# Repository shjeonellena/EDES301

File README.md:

# EDES301
EDES 301 Repository

# HexaForm Actuator Keyboard Test

This project provides a simple **keyboard-driven test interface** for the HexaForm prototype.  
Using a BeagleBone and GPIO control, you can:

- Turn an **air pump** on and off  
- Toggle **two solenoid valves** (Formation 1 and Formation 2)  
- See the current state and hints on a **16x2 HD44780 LCD** with an I²C backpack

It’s meant as a quick way to verify that wiring, drivers, and actuators are working as expected.

---

## Features

- Keyboard commands to control:
  - Pump (ON/OFF)
  - Solenoid 1 (Formation 1)
  - Solenoid 2 (Formation 2)
- Live status feedback on the HD44780 display:
  - Shows current action (e.g., `Pump ON`, `Formation 1`, `Turning off...`)
  - Shows which key to press to switch states (e.g., `OFF --> 2`)
- Safe shutdown:
  - Turns off all actuators
  - Clears the LCD and turns off the backlight
  - Calls `GPIO.cleanup()` on exit

---

## Hardware Overview

**Controller:**
- BeagleBone (e.g., BeagleBone Black / PocketBeagle)  
- GPIO pins used:
  - `P2_2` → Air pump (via ULN driver input)
  - `P2_4` → Solenoid 1 (via ULN driver input)
  - `P2_6` → Solenoid 2 (via ULN driver input)

**Actuation:**
- 1× Air pump
- 2× Solenoid valves  
- 1× ULN transistor array / driver (e.g., ULN2803A or similar) between GPIO and actuators
- External power supply for pump and solenoids (do **not** power them directly from the BeagleBone pins)

**Display:**
- HD44780-compatible 16x2 character LCD
- I²C backpack (e.g., PCF8574T)
- Connected to I²C bus on the BeagleBone
- Controlled via the `hd44780` CircuitPython-style library

---

## Software Requirements

On the BeagleBone:

- Python 3
- [`Adafruit_BBIO`](https://github.com/adafruit/adafruit-beaglebone-io-python) for GPIO
- `hd44780` (https://github.com/bablokb/circuitpython-hd44780/tree/master) library for controlling the LCD (the one used in:
  ```python
  import hd44780
  display = hd44780.HD44780()
  ```)

Make sure these are installed and importable in Python before running the script.

---

## File

The main script (for example):

```bash
actuator_keyboard_test.py

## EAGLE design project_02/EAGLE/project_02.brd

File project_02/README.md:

# Etch-A-Sketch PCB Design

This directory contains all design and manufacturing files for **Project 02**, which focuses on creating a custom printed circuit board (PCB) for the Etch-A-Sketch project. The board was designed to interface with a **PocketBeagle** and supports the electronics required for the implemented system.

All files necessary for **PCB fabrication, assembly, and documentation** are included in this repository.

---

## Repository Structure

### `/docs`
This folder contains supporting documentation for Project 02, including:
- The **Project 02 proposal**, outlining the design concept and system goals
- A **mechanical block diagram** describing the overall system architecture
- A **PDF of the finalized schematics**
- Images of the **layers** of the PCB layout for reference and review

---

### `/EAGLE`
This folder contains the full EAGLE design files used to create the PCB:
- **`.lbr`** – Custom and modified component libraries
- **`.sch`** – Schematic files defining the electrical design
- **`.brd`** – Board layout files defining component placement and routing

#### `/EAGLE/CAM Output`
The subfolder contains manufacturing outputs generated using **EAGLE’s default CAM settings**, including:
- **Gerber files** for PCB fabrication
- **Drill files** for vias and through-holes
- **Assembly files** for component placement and reference

These files can be directly submitted to a PCB manufacturer for production.

---

## Notes
- The PCB was designed with standard fabrication constraints in mind
- All silkscreen, copper, and drill layers have been verified prior to Gerber generation
- No additional processing is required before manufacturing

---

## Author
Ellena Jeon
Etch-A-Sketch Project – Project 02

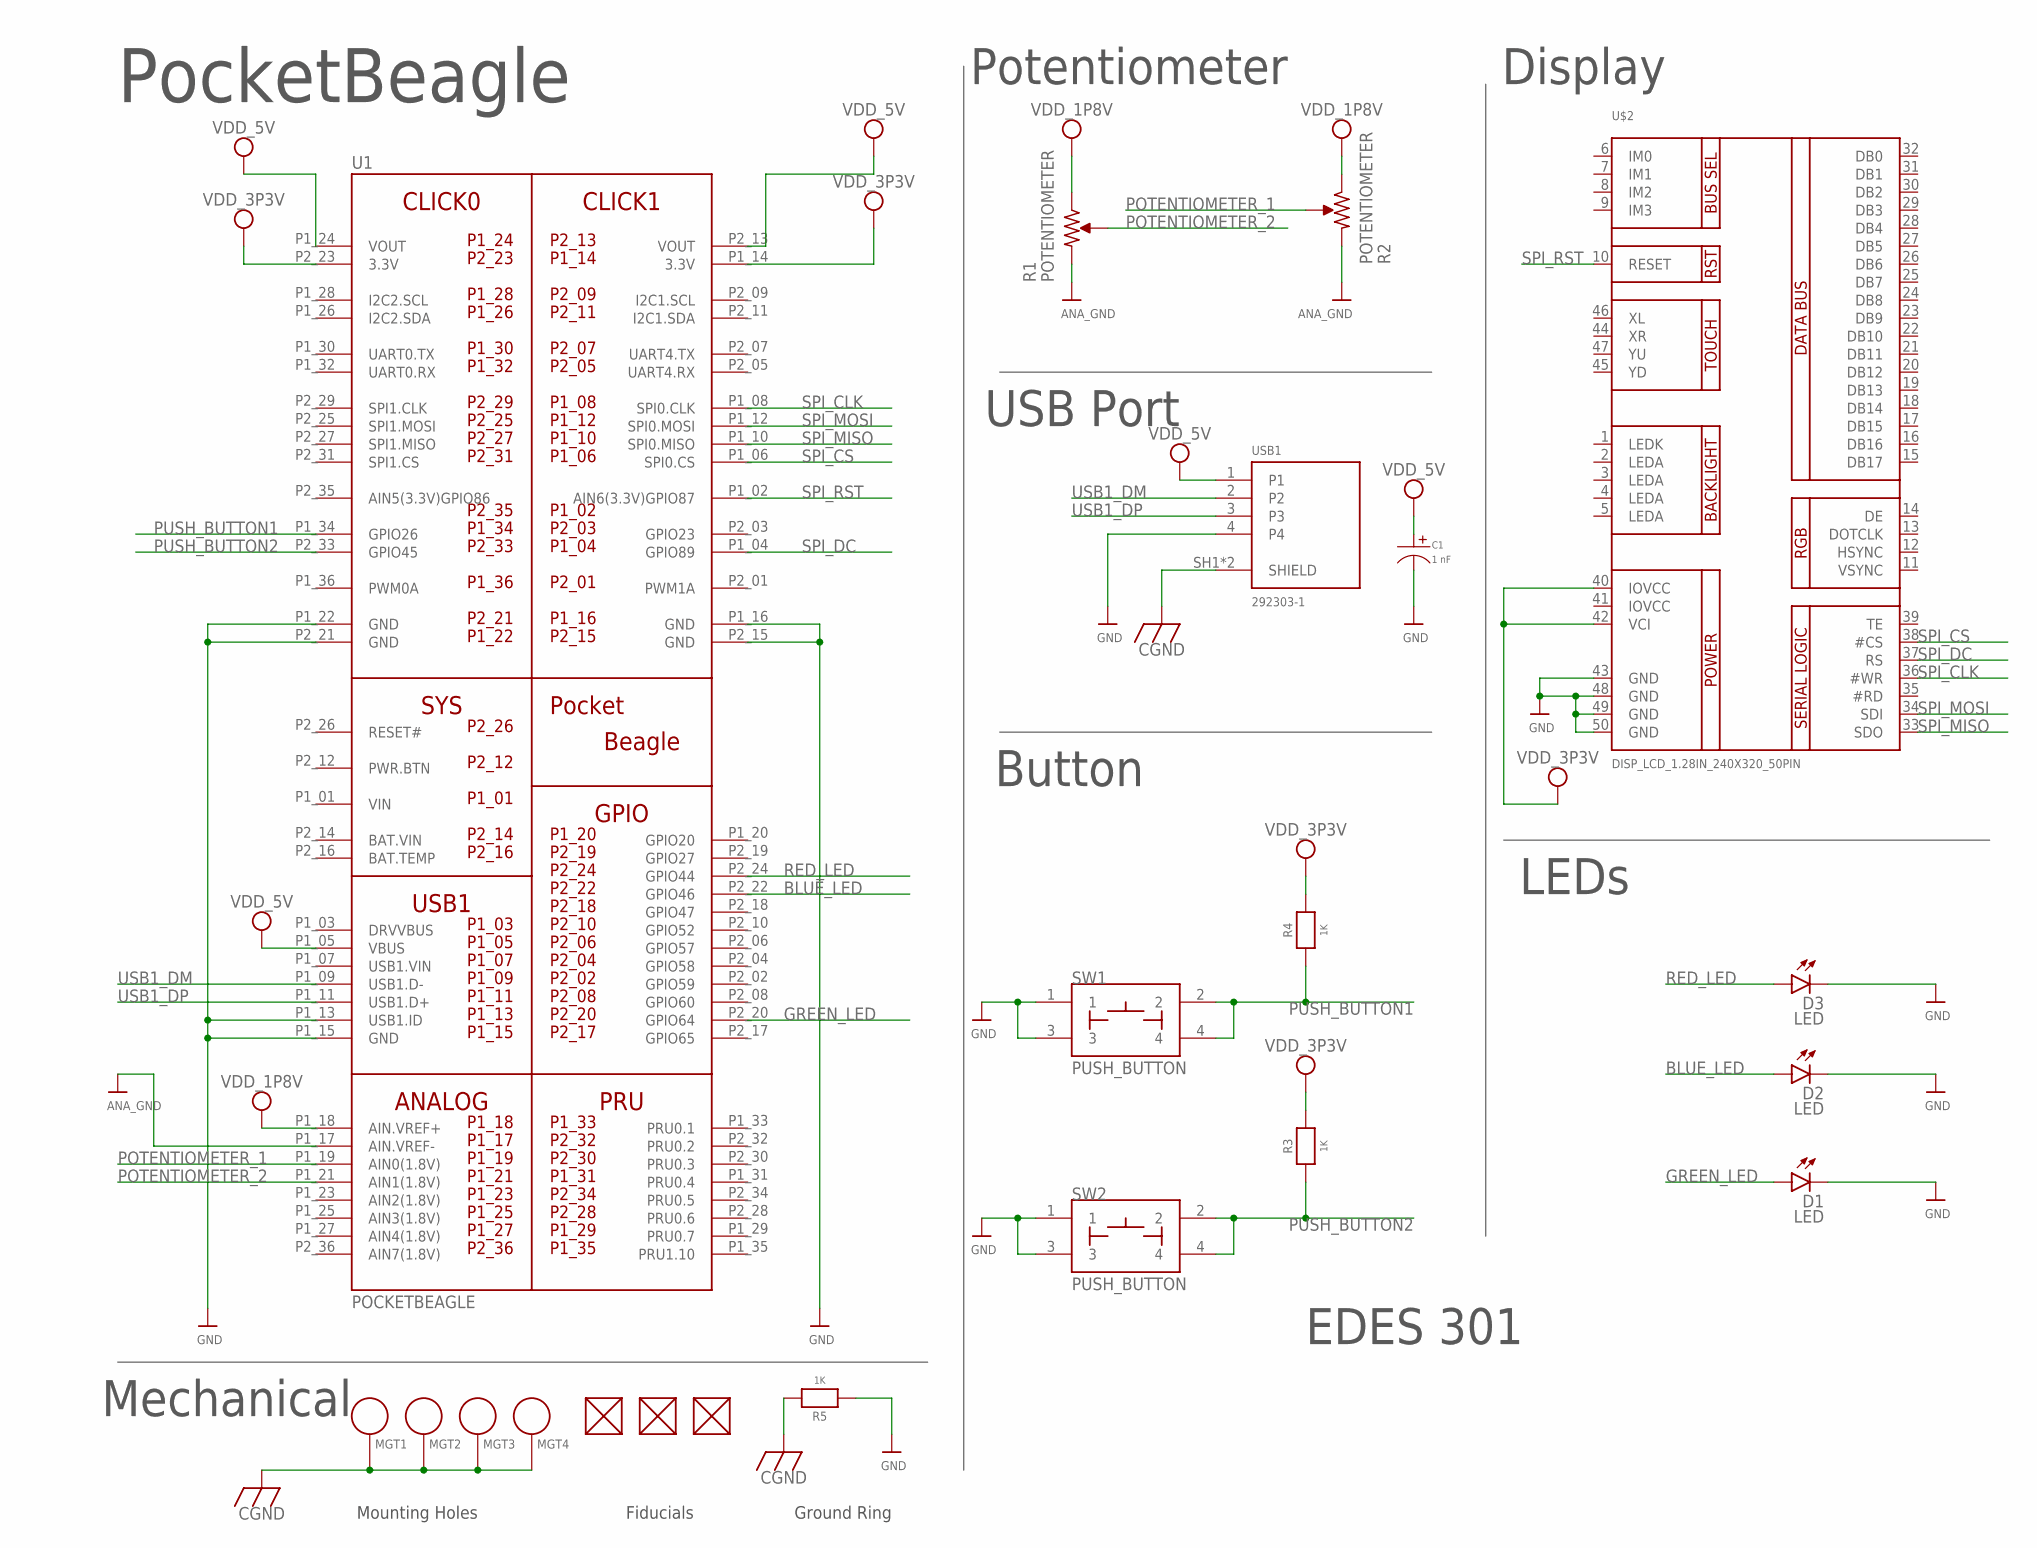
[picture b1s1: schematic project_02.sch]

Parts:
C1: 1 nF; CP4MM
D1, D2, D3: LED; LED3MM
FUD2, FUD3, FUD4: FIDUCIAL; FIDUCIAL_40MIL
MGT1, MGT2, MGT3, MGT4: MOUNTING_HOLE
R1, R2: POTENTIOMETER; POT-PO90S
R3, R4, R5: 1K; 0603-MINI
SW1, SW2: PUSH_BUTTON; BUTTON_12.5MM
U1: POCKETBEAGLE
U$2: DISP_LCD_1.28IN_240X320_50PIN; TFT_2.83IN_240X320_50PIN
USB1: 292303-1; TE_292303-1

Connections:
BAT.VIN: U1.P2_14 (BAT.VIN)
BLUE_LED: D2.A, U1.P2_22 (GPIO46)
CGND: MGT1.P$1, MGT2.P$1, MGT3.P$1, MGT4.P$1, R5.2, USB1.SH1 (SHIELD), USB1.SH2 (SHIELD)
GND: C1.P$2, D1.K (C), D2.K (C), D3.K (C), R1.CW, R2.CW, R5.1, SW1.1, SW1.3, SW2.1, SW2.3, U1.P1_13 (USB1.ID), U1.P1_15 (GND), U1.P1_16 (GND), U1.P1_17 (AIN.VREF-), U1.P1_22 (GND), U1.P2_15 (GND), U1.P2_21 (GND), U$2.43 (GND), U$2.48 (GND), U$2.49 (GND), U$2.50 (GND), USB1.4
GREEN_LED: D1.A, U1.P2_20 (GPIO64)
POTENTIOMETER_1: R2.S, U1.P1_19 (AIN0(1.8V))
POTENTIOMETER_2: R1.S, U1.P1_21 (AIN1(1.8V))
PUSH_BUTTON1: R4.1, SW1.2, SW1.4, U1.P1_34 (GPIO26)
PUSH_BUTTON2: R3.1, SW2.2, SW2.4, U1.P2_33 (GPIO45)
RED_LED: D3.A, U1.P2_24 (GPIO44)
SPI_CLK: U1.P1_08 (SPI0.CLK), U$2.36 (#WR)
SPI_CS: U1.P1_06 (SPI0.CS), U$2.38 (#CS)
SPI_DC: U1.P1_04 (GPIO89), U$2.37 (RS)
SPI_MISO: U1.P1_10 (SPI0.MISO), U$2.33 (SDO)
SPI_MOSI: U1.P1_12 (SPI0.MOSI), U$2.34 (SDI)
SPI_RST: U1.P1_02 (AIN6(3.3V)GPIO87), U$2.10 (RESET)
USB1_DM: U1.P1_09 (USB1.D-), USB1.2
USB1_DP: U1.P1_11 (USB1.D+), USB1.3
VDD_1P8V: R1.CCW, R2.CCW, U1.P1_18 (AIN.VREF+)
VDD_3P3V: R3.2, R4.2, U1.P1_14 (3.3V), U1.P2_23 (3.3V), U$2.40 (IOVCC), U$2.42 (VCI)
VDD_5V: C1.P$1, U1.P1_05 (VBUS), U1.P1_24 (VOUT), U1.P2_13 (VOUT), USB1.1
VIN: U1.P1_01 (VIN)

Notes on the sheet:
PocketBeagle
Potentiometer
USB Port
Button
Display
LEDs
EDES 301
Mechanical
Mounting Holes
Fiducials
Ground Ring

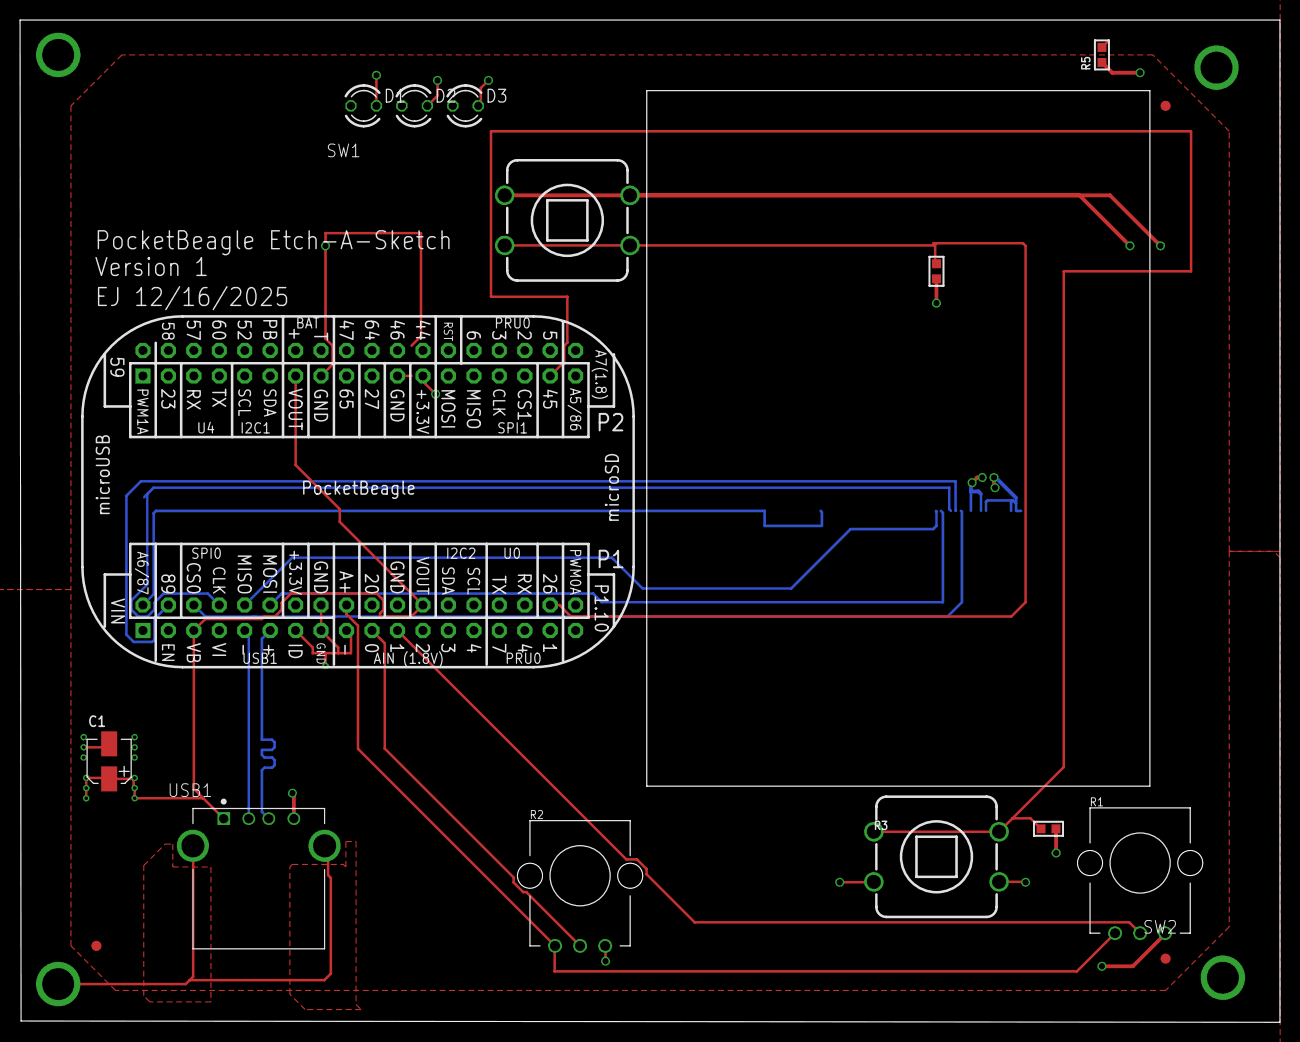
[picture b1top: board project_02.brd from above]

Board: 4 copper layers, 125.7 x 100.0 mm, 21 parts (0 on the bottom side), 20 nets.

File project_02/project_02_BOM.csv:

Qty,Value,Device,Package,Parts,Description,AVAILABILITY,CENTERLINE_PITCH,CHECK_PRICES,COMMENT,DESCRIPTION,EU_ROHS_COMPLIANCE,HOUSEPART,MF,MP,MPN,NUMBER_OF_POSITIONS,PACKAGE,POPULARITY,POPULATE,PRICE,PRODUCT_TYPE,PURCHASE-URL,SNAPEDA_LINK,TOLERANCE,URL,VOLTAGE,
1,1 nF,CAPACITOR_P_4MM,CP4MM,C1,Library:  MF_Passives,,,,,,,,,,,,,,1,,,,,,,,
3,1K,RESISTOR0603MINI,0603-MINI,"R3, R4, R5",Resistors,,,,,,,,,,,,,,,,,,,,,,
1,292303-1,292303-1,TE_292303-1,USB1,Check availability,In Stock,2 mm[.078 in],https://www.snapeda.com/parts/292303-1/TE+Connectivity+AMP+C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,292303-1,Type A Standard USB Connector 4 Position Right Angle Mount 1 Port | TE Connectivity 292303-1,Compliant,,TE Connectivity,292303-1,,4,None,,,None,Connector,https://www.snapeda.com/api/url_track_click_mouser/?unipart_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 Connectivity&part_name=292303-1&search_term=292303-1,https://www.snapeda.com/parts/292303-1/TE+Connectivity+AMP+C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,,,,
1,DISP_LCD_1.28IN_240X320_50PIN,DISP_LCD_1.28IN_240X320_50PIN,TFT_2.83IN_240X320_50PIN,U$2,,,,,,,,,,,,,,,,,,,,,,,
3,FIDUCIAL,FIDUCIAL,FIDUCIAL_40MIL,"FUD2, FUD3, FUD4",,,,,,,,,,,,,,,,,,,,,,,
3,LED,LED_13MM,LED3MM,"D1, D2, D3",LED,,,,,,,,,,,,,97,,,,,,,,,
4,MOUNTING_HOLE,MOUNTING_HOLE,MOUNTING_HOLE,"MGT1, MGT2, MGT3, MGT4",Chassis Mounting Hole w/GND connection ability,,,,,,,,,,,,,,,,,,,,,,
1,POCKETBEAGLE,POCKETBEAGLE,POCKETBEAGLE,U1,,,,,,,,,,,,,,,,,,,,,,,
2,POTENTIOMETER,POTENTIOMETER,POT-PO90S,"R1, R2",Potentiometer - Examples:,,,,,,,,,,,,,,,,,,,,,,
2,PUSH_BUTTON,PUSH_BUTTON,BUTTON_12.5MM,"SW1, SW2",,,,,,,,,,,,,,,,,,,,,,,

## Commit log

2025-10-07 Add blink_USR3.py (5 Hz USR3 blink) and project structure
2025-10-07 Initial commit: added python folder with blink_led and simple_calc labs
2025-10-07 Button driver
2025-12-02 Update project title and description in README
2025-12-02 add .gitignore to ignore .DS_Store
2025-12-02 add project_01 folder
2025-12-16 Revise PCB layout descriptions
    Updated PCB layout references and folder naming.
